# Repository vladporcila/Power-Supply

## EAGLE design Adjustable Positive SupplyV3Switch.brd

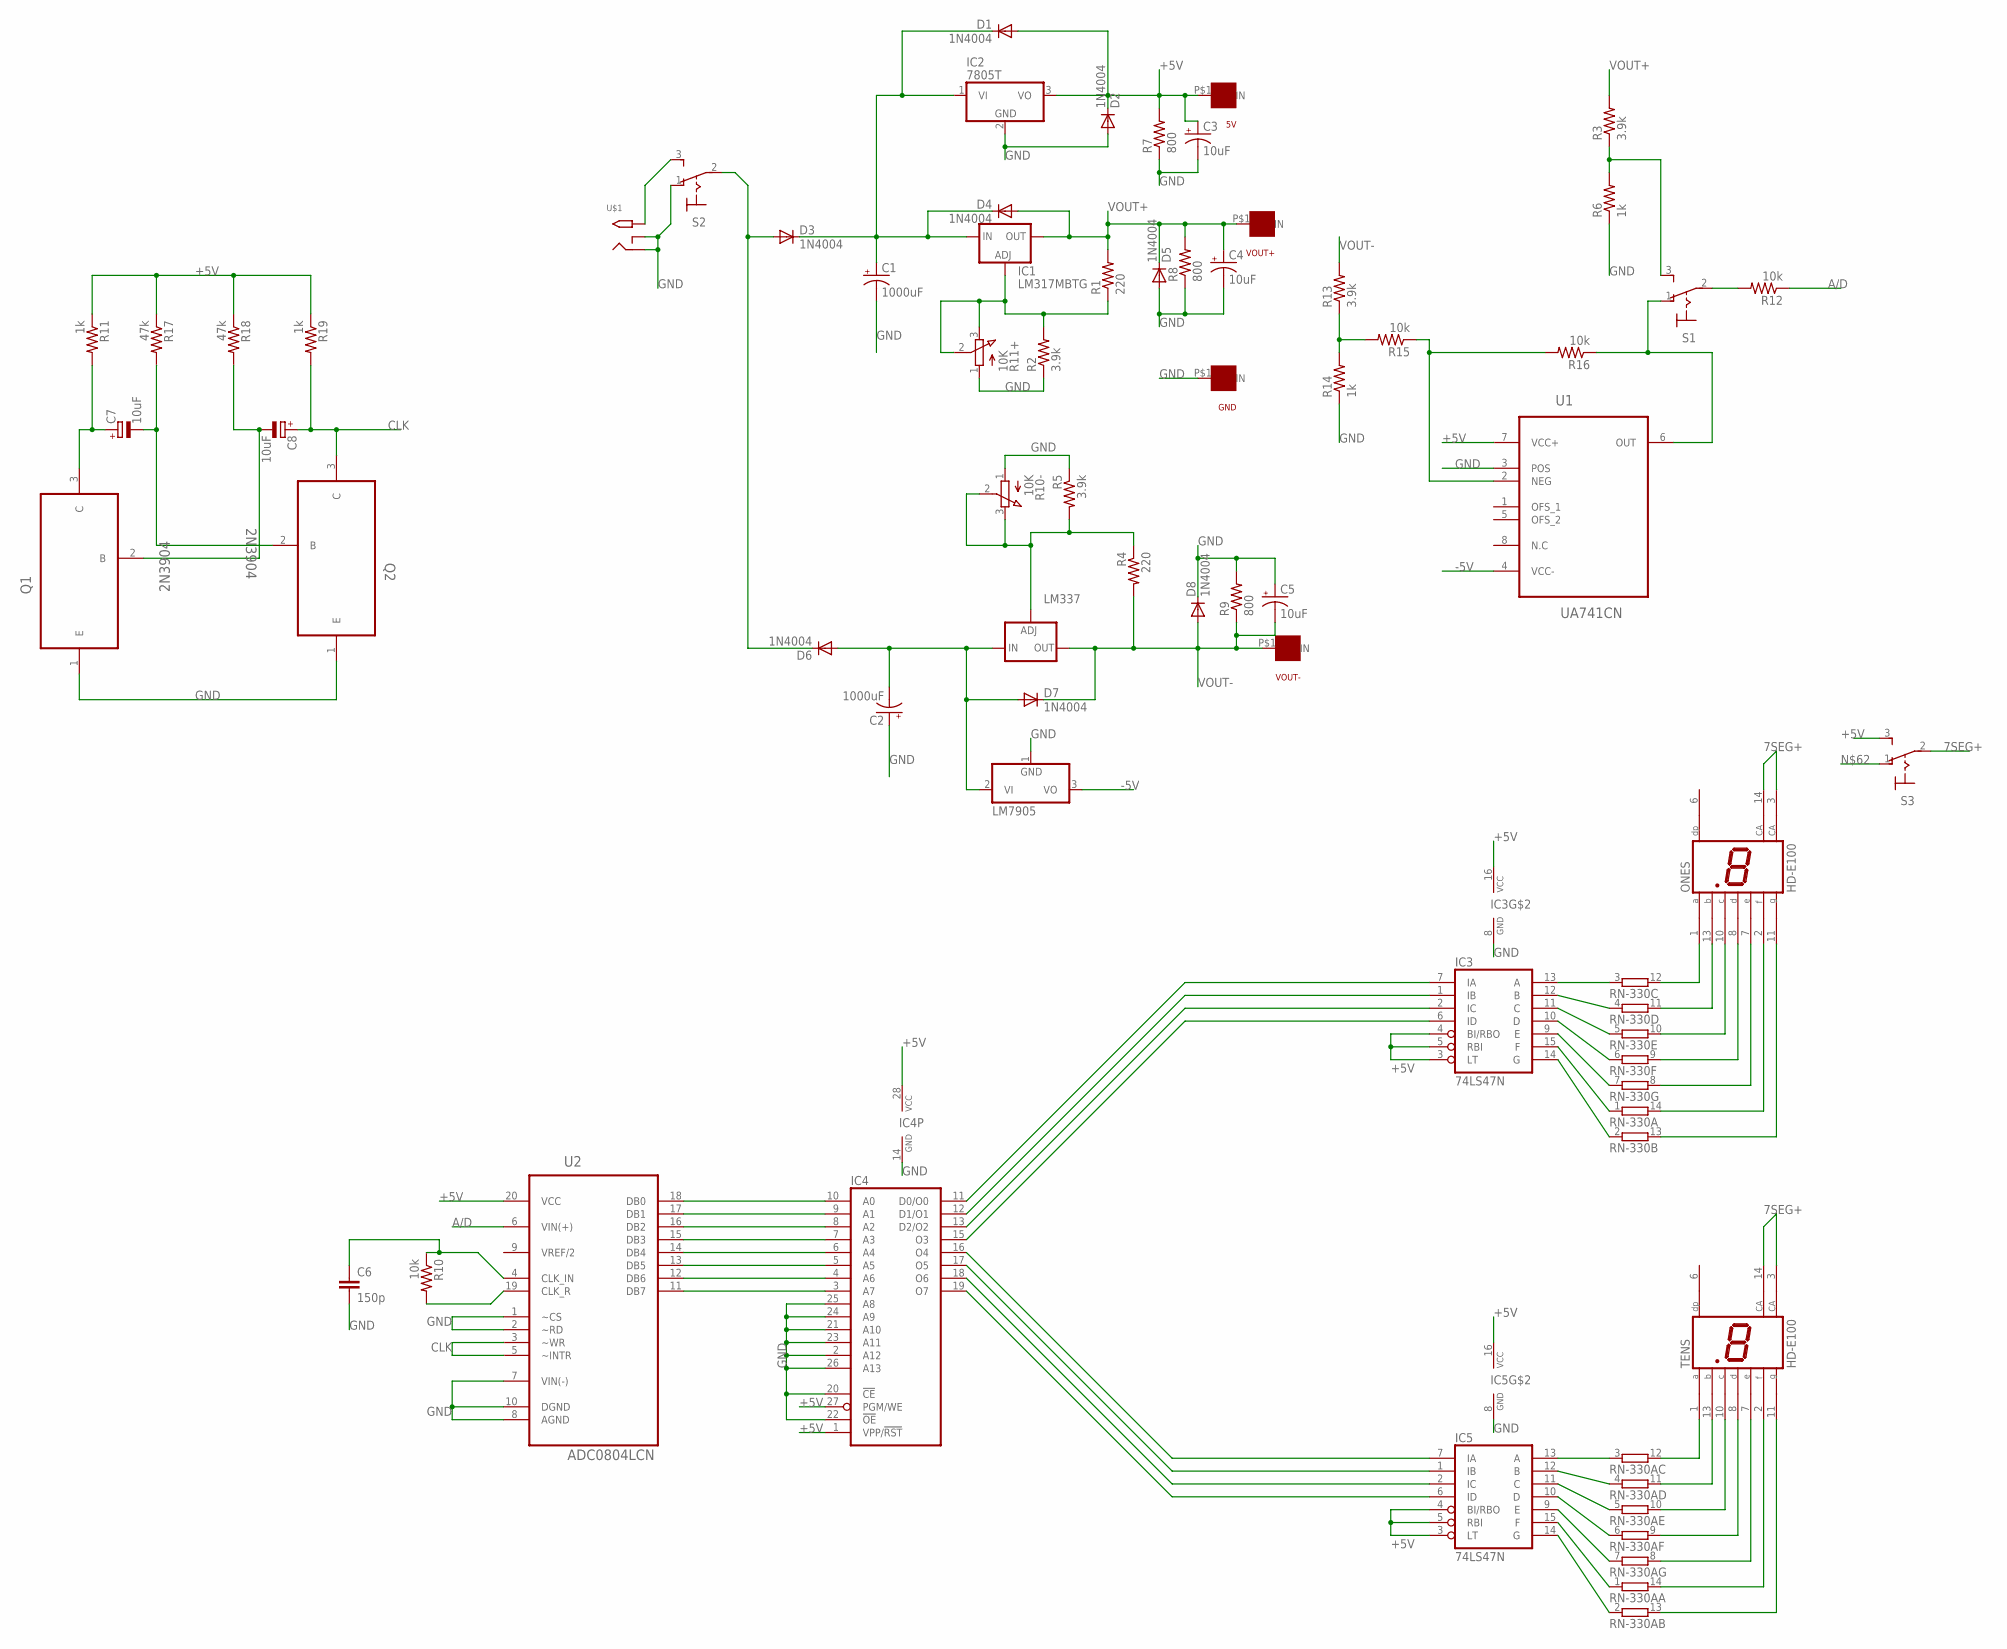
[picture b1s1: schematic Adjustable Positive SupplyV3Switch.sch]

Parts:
5V: TURRENT_TERMINAL; TURRET_CONNECTOR
C1, C2: 1000uF; E7,5-16
C3, C4, C5: 10uF; E2,5-5
C6: 150p; C025-025X050
C7, C8: 10uF; B45181B
D1, D2, D3, D4, D5, D6, D7, D8: 1N4004; DO41-10
GND: TURRENT_TERMINAL; TURRET_CONNECTOR
IC1: LM317MBTG; TO220L1
IC2: 7805T; TO220H
IC3, IC5: 74LS47N; DIL16
IC4: 27011; DIL28
LM337: LM337TL; 337TL
LM7905: 7905T; TO220H
ONES: HD-E100; HDSP-I
Q1, Q2: 2N3904; TO254P508X877-3
R1, R4: 220; 0411/15
R2, R3, R5, R13: 3.9k; 0411/15
R6, R11, R14, R19: 1k; 0411/15
R7, R8, R9: 800; 0411/15
R10, R12, R15, R16: 10k; 0411/15
R10-, R11+: 10K; EVUE
R17, R18: 47k; 0411/15
RN-330, RN-330A: 7R-N; DIL14
S1, S2, S3: M9040P
TENS: HD-E100; HDSP-I
U1: UA741CN; DIP254P762X533-8
U2: ADC0804LCN; DIP254P762X508-20
U$1: 2.1MMJACKTHM; PJ-102A
VOUT+: TURRENT_TERMINAL; TURRET_CONNECTOR
VOUT-: TURRENT_TERMINAL; TURRET_CONNECTOR

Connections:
7SEG+: ONES.3 (CA), ONES.14 (CA), S3.2, TENS.3 (CA), TENS.14 (CA)
+5V: 5V.P$1, C3.+, D1.A, D2.C, IC2.3 (VO), IC3.3 (LT), IC3.4 (BI/RBO), IC3.5 (RBI), IC3.16 (VCC), IC4.1 (VPP/!RST), IC4.27 (PGM/WE), IC4.28 (VCC), IC5.3 (LT), IC5.4 (BI/RBO), IC5.5 (RBI), IC5.16 (VCC), R7.2, R11.1, R17.1, R18.1, R19.1, S3.3 (S), U1.7 (VCC+), U2.20 (VCC)
-5V: LM7905.3 (VO), U1.4 (VCC-)
A/D: R12.1, U2.6 (VIN(+))
CLK: C8.+, Q2.3 (C), R19.2, U2.3 (~WR), U2.5 (~INTR)
GND: C1.-, C2.+, C3.-, C4.-, C5.+, C6.2, D2.A, D5.A, D8.C, GND.P$1, IC2.2 (GND), IC3.8 (GND), IC4.2 (A12), IC4.14 (GND), IC4.20 (!CE), IC4.21 (A10), IC4.22 (!OE), IC4.23 (A11), IC4.24 (A9), IC4.25 (A8), IC4.26 (A13), IC5.8 (GND), LM7905.1 (GND), Q1.1 (E), Q2.1 (E), R2.1, R5.1, R6.1, R7.1, R8.1, R9.2, R10-.1 (A), R11+.1 (A), R14.1, S2.1 (O), U1.3 (POS), U2.1 (~CS), U2.2 (~RD), U2.7 (VIN(-)), U2.8 (AGND), U2.10 (DGND), U$1.RING, U$1.RING_SW
unnamed: R12.2, S1.2
unnamed: D3.A, D6.C, S2.2
unnamed: C1.+, D1.C, D3.C, D4.C, IC1.3 (IN), IC2.1 (VI)
unnamed: IC1.1 (ADJ), R1.1, R2.2, R11+.2 (S), R11+.3 (E)
unnamed: R3.1, R6.2, S1.3 (S)
unnamed: LM337.1 (ADJ), R4.1, R5.2, R10-.2 (S), R10-.3 (E)
unnamed: R13.1, R14.2, R15.2
unnamed: R15.1, R16.2, U1.2 (NEG)
unnamed: C2.-, D6.A, D7.A, LM337.2 (IN), LM7905.2 (VI)
unnamed: R16.1, S1.1 (O), U1.6 (OUT)
unnamed: IC4.16 (O4), IC5.7 (IA)
unnamed: IC4.18 (O6), IC5.2 (IC)
unnamed: IC4.19 (O7), IC5.6 (ID)
unnamed: IC3.7 (IA), IC4.11 (D0/O0)
unnamed: IC3.1 (IB), IC4.12 (D1/O1)
unnamed: IC3.2 (IC), IC4.13 (D2/O2)
unnamed: IC3.6 (ID), IC4.15 (O3)
unnamed: IC3.15 (F), RN-330.1
unnamed: IC3.14 (G), RN-330.2 (1)
unnamed: IC3.13 (A), RN-330.3 (1)
unnamed: IC3.12 (B), RN-330.4 (1)
unnamed: IC3.11 (C), RN-330.5 (1)
unnamed: IC3.10 (D), RN-330.6 (1)
unnamed: IC3.9 (E), RN-330.7 (1)
unnamed: ONES.1 (A), RN-330.12 (2)
unnamed: ONES.13 (B), RN-330.11 (2)
unnamed: ONES.10 (C), RN-330.10 (2)
unnamed: ONES.8 (D), RN-330.9 (2)
unnamed: ONES.7 (E), RN-330.8 (2)
unnamed: RN-330A.8 (2), TENS.7 (E)
unnamed: ONES.2 (F), RN-330.14 (2)
unnamed: IC5.15 (F), RN-330A.1
unnamed: IC5.14 (G), RN-330A.2 (1)
unnamed: IC5.13 (A), RN-330A.3 (1)
unnamed: IC5.12 (B), RN-330A.4 (1)
unnamed: ONES.11 (G), RN-330.13 (2)
unnamed: IC5.11 (C), RN-330A.5 (1)
unnamed: IC5.10 (D), RN-330A.6 (1)
unnamed: IC5.9 (E), RN-330A.7 (1)
unnamed: IC4.17 (O5), IC5.1 (IB)
unnamed: RN-330A.12 (2), TENS.1 (A)
unnamed: RN-330A.11 (2), TENS.13 (B)
unnamed: RN-330A.10 (2), TENS.10 (C)
unnamed: RN-330A.9 (2), TENS.8 (D)
unnamed: RN-330A.14 (2), TENS.2 (F)
unnamed: RN-330A.13 (2), TENS.11 (G)
unnamed: IC4.10 (A0), U2.18 (DB0)
unnamed: IC4.9 (A1), U2.17 (DB1)
unnamed: IC4.8 (A2), U2.16 (DB2)
unnamed: IC4.7 (A3), U2.15 (DB3)
unnamed: IC4.6 (A4), U2.14 (DB4)
unnamed: IC4.5 (A5), U2.13 (DB5)
unnamed: IC4.4 (A6), U2.12 (DB6)
unnamed: IC4.3 (A7), U2.11 (DB7)
unnamed: R10.2, U2.19 (CLK_R)
unnamed: C6.1, R10.1, U2.4 (CLK_IN)
unnamed: C7.+, Q1.3 (C), R11.2
unnamed: C7.-, Q2.2 (B), R17.2
unnamed: S2.3 (S), U$1.TIP
unnamed: C8.-, Q1.2 (B), R18.2
VOUT+: C4.+, D4.A, D5.C, IC1.2 (OUT), R1.2, R3.2, R8.2, VOUT+.P$1
VOUT-: C5.-, D7.C, D8.A, LM337.3 (OUT), R4.2, R9.1, R13.2, VOUT-.P$1

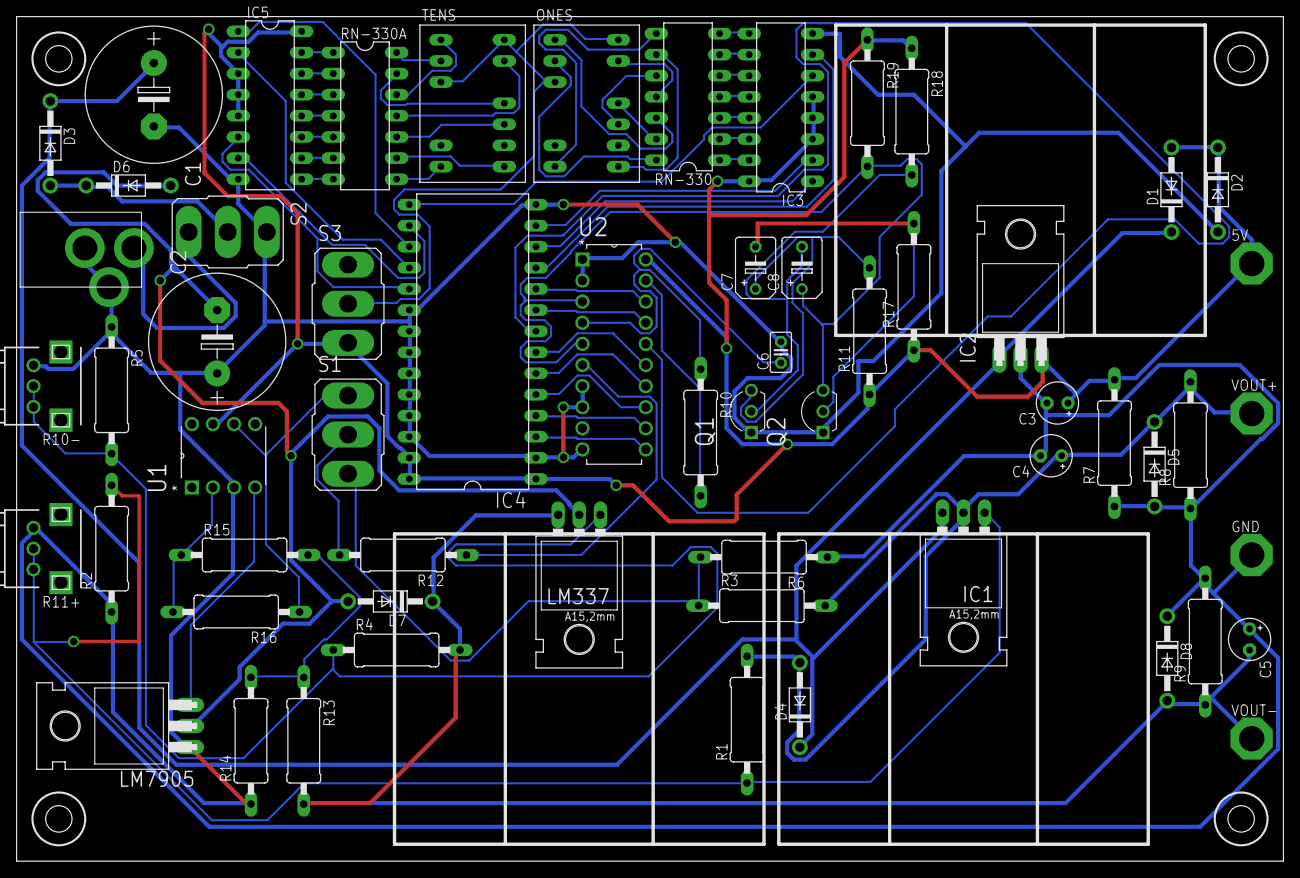
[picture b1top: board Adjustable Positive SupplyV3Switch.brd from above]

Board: 2 copper layers, 152.4 x 101.6 mm, 60 parts (0 on the bottom side), 68 nets.

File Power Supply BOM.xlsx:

Qty per Board | Value | Device | Package | Parts | Description | MPN | Price Per unit | Total Per Unit |  | x60 | Price Per unit
1 |  | 7905T | TO220H | LM7905 | Negative VOLTAGE REGULATOR | LM7905CT | 0.81 | 0.81 |  | 60 | 0.626 | 0.626
2 |  | 7R-N | DIL14 | RN-330 | DIL RESISTOR | 4114R-1-331LF | 1.1000000000000001 | 2.2000000000000002 |  | 120 | 0.80959999999999999 | 1.6192
1 |  | LM337TL | 337TL | LM337 | VOLTAGE REGULATOR | LM337KCSE3 | 1.19 | 1.19 |  | 60 | 0.94299999999999995 | 0.94299999999999995
1 |  | M9040P | M9040P | S1 | TOGGLE SWITCH | M2012SS1W01 | 4.76 | 4.76 |  | 60 | 4.1673999999999998 | 4.1673999999999998
2 | 1000uF | CPOL-USE7.5-16 | E7,5-16 | C1, C2 | POLARIZED CAPACITOR, American symbol | EKY-500ELL102ML25S | 1.68 | 3.36 |  | 120 | 0.98350000000000004 | 1.9670000000000001
2 | 10K | EVUE2A | EVUE | R10-, R11+ | 9 mm Square Rotary Potentiometers | 3310C-001-103L | 3.74 | 7.48 |  | 120 | 2.7031999999999998 | 5.4063999999999997
6 | 10k | R-US_0411/15 | 0411/15 | R12, R15, R16, R17, R18, R19 | RESISTOR, American symbol | CF14JT10K0 | 0.14000000000000001 | 0.84000000000000008 |  | 360 | 2.3199999999999998E-2 | 0.13919999999999999
8 | 1N4004 | 1N4004 | DO41-10 | D1, D2, D3, D4, D5, D6, D7, D8 | DIODE | 1N4004-G | 0.15 | 1.2 |  | 480 | 5.1279999999999999E-2 | 0.41023999999999999
2 | 1k | R-US_0411/15 | 0411/15 | R6, R14 | RESISTOR, American symbol | CF14JT1K00 | 0.14000000000000001 | 0.28000000000000003 |  | 120 | 3.1300000000000001E-2 | 6.2600000000000003E-2
1 | 2.1MMJACKTHM | 2.1MMJACKTHM | PJ-102A | U$1 | 2.1mm x 5.5mm THM DC jack with internal switch. Digikey part #PJ-102A, 4UCON pa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 | PJ-002A | 1.26 | 1.26 |  | 60 | 0.873 | 0.873
3 | 10uF |  |  | C3,C4,C5 | Electrolytic Cap | EEU-EB1H100S | 0.4 | 1.2000000000000002 |  | 180 | 0.15690000000000001 | 0.47070000000000001
2 | 220 | R-US_0411/15 | 0411/15 | R1, R4 | RESISTOR, American symbol | CF14JT220R | 0.14000000000000001 | 0.28000000000000003 |  | 120 | 3.1300000000000001E-2 | 6.2600000000000003E-2
2 | 2N3904 | 2N3904 | TO254P508X877-3 | Q1, Q2 | NPN General Purpose Amplifier | 2N3904-AP | 0.26 | 0.52 |  | 120 | 0.14910000000000001 | 0.29820000000000002
4 | 3.9k | R-US_0411/15 | 0411/15 | R2, R3, R5, R13 | RESISTOR, American symbol | CF14JT3K90 | 0.14000000000000001 | 0.56000000000000005 |  | 240 | 3.1300000000000001E-2 | 0.12520000000000001
1 | 74LS47N | 74LS47N | DIL16 | IC3 | BCD to seven segment DECODER/DRIVER | SN74LS47N | 2.5299999999999998 | 2.5299999999999998 |  | 60 | 2.0110000000000001 | 2.0110000000000001
1 | 7805T | 7805T | TO220H | IC2 | Positive VOLTAGE REGULATOR | MC7805CT-BP | 0.65 | 0.65 |  | 60 | 0.46920000000000001 | 0.46920000000000001
3 | 800 | R-US_0411/15 | 0411/15 | R7, R8, R9 | RESISTOR, American symbol | CF14JT820R | 0.14000000000000001 | 0.42000000000000004 |  | 180 | 3.1300000000000001E-2 | 9.3900000000000011E-2
2 | HD-E100 | HD-E100 | HDSP-I | DISONES, DISTENS | LED DISPLAY | LTS-312AHR | 1.82 | 3.64 |  | 120 | 1.0183 | 2.0366
1 | LM317MBTG | LM317MBTG | TO220L1 | IC1 | 500 mA Adjustable Output Positive Voltage Regulator | LM317T | 0.96 | 0.96 |  | 60 | 0.73799999999999999 | 0.73799999999999999
1 | PIC16F688-I/P | PIC16F688-I/P | DIP254P762X533-14 | U$2 | CMOS Microcontrollers | PIC16F688-I/P | 2.2599999999999998 | 2.2599999999999998 |  | 60 | 1.8236000000000001 | 1.8236000000000001
4 | TURRENT_TERMINAL | TURRENT_TERMINAL | TURRET_CONNECTOR | 5V, GND, VOUT+, VOUT- |  | H9004-01 | 0.53 | 2.12 |  | 240 | 0.34499999999999997 | 1.38
1 | UA741CN | UA741CN | DIP254P762X533-8 | U1 | operational amplifiers | UA741CP | 0.74 | 0.74 |  | 60 | 0.56599999999999995 | 0.56599999999999995
1 | 8pin socket |  |  |  |  | A08-LC-TT | 0.24 | 0.24 |  | 60 | 0.17280000000000001 | 0.17280000000000001
1 | 16 pin socket |  |  |  |  | A16-LC-TT | 0.34 | 0.34 |  | 60 | 0.2366 | 0.2366
3 | TO-220 Heatsink |  |  |  |  | V2008B | 0.91 | 2.73 |  | 180 | 0.65680000000000005 | 1.9704000000000002
1 | Bannana Plugs BLACK |  |  |  |  | 108-0903-001 | 0.95 | 0.95 |  | 60 | 0.78439999999999999 | 0.78439999999999999
2 | Knobs |  |  |  |  | MPKG40B18 | 2.67 | 5.34 |  | 120 | 2.081 | 4.1619999999999999
3 | Bannana Plugs RED |  |  |  |  | 108-0902-001 | 0.95 | 2.8499999999999996 |  | 180 | 0.66239999999999999 | 1.9872000000000001
4 | Standoffs |  |  |  |  | 4803 | 0.86 | 3.44 |  | 240 | 0.49409999999999998 | 1.9763999999999999
8 | Standoffs |  |  |  |  | 4801 | 0.8 | 6.4 |  | 480 | 0.42548000000000002 | 3.4038400000000002
1 | 14 pin socket |  |  |  |  | A14-LC-TT | 0.3 | 0.3 |  | 60 | 0.2102 | 0.2102
1 | AC Adapter |  |  |  |  | BPD2F | 19.3 | 19.3 |  | 60 | 19.149999999999999 | 19.149999999999999
 |  |  |  |  |  |  |  | 81.149999999999991 |  |  |  | 60.342880000000001

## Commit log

2016-09-29 :space_invader: Added .gitattributes & .gitignore files
2016-09-29 Power Supply
    Power Supply
